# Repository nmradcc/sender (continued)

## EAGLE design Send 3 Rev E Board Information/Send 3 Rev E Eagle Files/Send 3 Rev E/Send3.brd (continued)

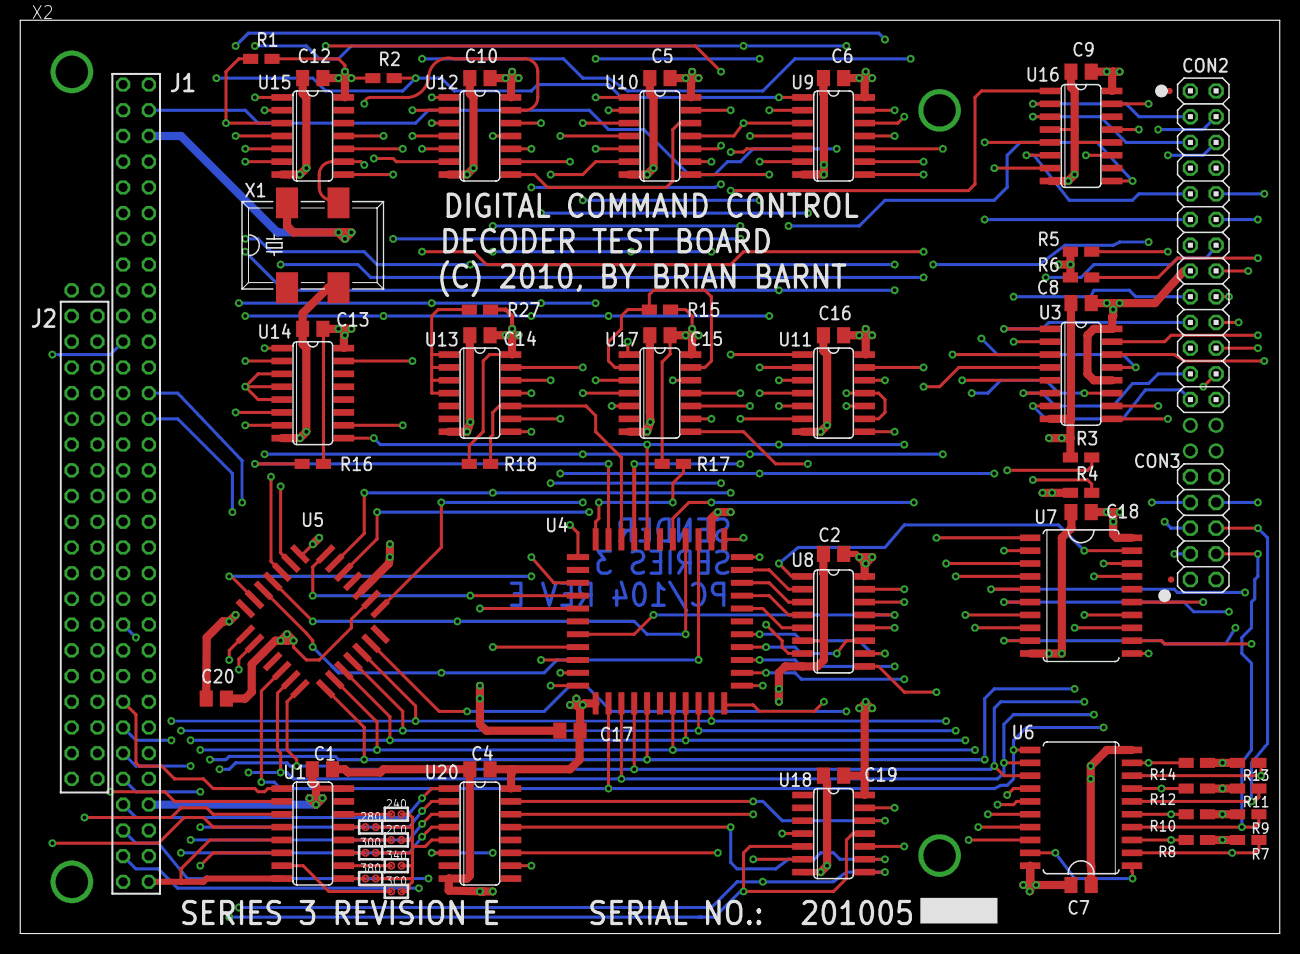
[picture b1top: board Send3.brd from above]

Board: 4 copper layers, 124.4 x 90.2 mm, 67 parts (0 on the bottom side), 118 nets.

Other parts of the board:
U$5: BORDER_AL

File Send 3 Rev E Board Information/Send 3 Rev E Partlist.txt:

Partlist

Exported from Send3.sch at 6/14/2019 9:57 PM

EAGLE Version 9.2.2 Copyright (c) 1988-2018 Autodesk, Inc.

Assembly variant: 

Part     Value          Device            Package        Library     Sheet

C1                      C-USC0805K        C0805K         Project Lib 2
C2                      C-USC0805K        C0805K         Project Lib 2
C4                      C-USC0805K        C0805K         Project Lib 3
C5                      C-USC0805K        C0805K         Project Lib 4
C6                      C-USC0805K        C0805K         Project Lib 6
C7                      C-USC0805K        C0805K         Project Lib 6
C8                      C-USC0805K        C0805K         Project Lib 6
C9                      C-USC0805K        C0805K         Project Lib 6
C10                     C-USC0805K        C0805K         Project Lib 4
C12                     C-USC0805K        C0805K         Project Lib 3
C13                     C-USC0805K        C0805K         Project Lib 4
C14                     C-USC0805K        C0805K         Project Lib 4
C15                     C-USC0805K        C0805K         Project Lib 4
C16                     C-USC0805K        C0805K         Project Lib 4
C17                     C-USC0805K        C0805K         Project Lib 5
C18                     C-USC0805K        C0805K         Project Lib 5
C19                     C-USC0805K        C0805K         Project Lib 5
C20                     C-USC0805K        C0805K         Project Lib 5
CON2                    PINHD-2X13        2X13           pinhead     6
CON3                    PINHD-2X5         2X05           pinhead     6
JMPR2                   JUMPER            SOLDER_BRIDGE  Project Lib 2
JMPR3                   JUMPER            SOLDER_BRIDGE  Project Lib 2
JMPR4                   JUMPER            SOLDER_BRIDGE  Project Lib 2
JMPR5                   JUMPER            SOLDER_BRIDGE  Project Lib 2
JMPR6                   JUMPER            SOLDER_BRIDGE  Project Lib 2
JMPR7                   JUMPER            SOLDER_BRIDGE  Project Lib 2
JMPR8                   JUMPER            SOLDER_BRIDGE  Project Lib 2
R1       10K            R-US_0805W        R0805W         Project Lib 5
R2       10K            R-US_0805W        R0805W         Project Lib 5
R3       10K            R-US_0805W        R0805W         Project Lib 6
R4       10K            R-US_0805W        R0805W         Project Lib 6
R5       10K            R-US_0805W        R0805W         Project Lib 6
R6       10K            R-US_0805W        R0805W         Project Lib 6
R7       10K            R-US_0805W        R0805W         Project Lib 6
R8       10K            R-US_0805W        R0805W         Project Lib 6
R9       10K            R-US_0805W        R0805W         Project Lib 6
R10      10K            R-US_0805W        R0805W         Project Lib 6
R11      10K            R-US_0805W        R0805W         Project Lib 6
R12      10K            R-US_0805W        R0805W         Project Lib 6
R13      10K            R-US_0805W        R0805W         Project Lib 6
R14      10K            R-US_0805W        R0805W         Project Lib 6
R15      10K            R-US_0805W        R0805W         Project Lib 4
R16      10K            R-US_0805W        R0805W         Project Lib 3
R17      10K            R-US_0805W        R0805W         Project Lib 3
R18      10K            R-US_0805W        R0805W         Project Lib 3
R27      10K            R-US_0805W        R0805W         Project Lib 5
U1       74AHC138D      74AHC138D         SO16           Project Lib 2
U3       AM26C32CD      AM26C32CD         SO16           Project Lib 6
U4                      8255A-S           PLCC44         Project Lib 3
U5       8254           8254              PLCC28S        Project Lib 4
U6       74ACT540       74540             SO20W          Project Lib 6
U7       74LS273DW      74LS273DW         SO20W          74xx-us     6
U8       74HCT166D      74HCT166D         SO16           Project Lib 5
U9       74ACT74D       7474D             SO14           Project Lib 5
U10      74ACT08D       74AC08D           SO14           Project Lib 4
U11      74ACT02D       74AC02D           SO14           Project Lib 4
U12      74ACT00D       74AC00D           SO14           Project Lib 4
U13      74ACT74D       7474D             SO14           Project Lib 5
U14      74ACT161D      74161D            SO16           Project Lib 5
U15      74AC04D        74AC04D           SO14           Project Lib 3
U16      AM26C31CD      AM26C31CD         SO16           Project Lib 6
U17      74ACT74D       7474D             SO14           Project Lib 4
U18      74ACT02D       74ACT02D          SO14           Project Lib 3
U20      74AHC138D      74AHC138D         SO16           Project Lib 2
X1                      CRYSTAL_RES-1100S 1100S          crystal     4
X2       PC104_CARD1    PC104_CARD1       PC104-STANDARD Project Lib 2

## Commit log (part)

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2020-06-02 Add the default color to the color tables
2020-06-02 Add a Major Tasks section
2020-06-02 Add options to help to all of the sub-catagories Remove the led command and make it a variable Use ResetColor when restoring the previous color
2020-06-02 Use ResetColor when restoring the previous color Use the default background color in dir
2020-06-02 Zero copy packet queue for the DCC track generator
2020-10-26 Dont wait for IsPacketComplete
2020-10-26 Dont wait
2020-10-26 Change timer to 32 bit
2020-10-26 Change to 32 bit timer
2020-10-26 Change script task stack size
2020-10-26 Add HAL_UART_ReceiveReady
2020-10-26 Put a V4 ifdef around time
2020-10-26 Lots of porting changes
2020-10-26 Fix all the build packet calls for 32 bit
2020-10-26 Change to 32 bit timers
2020-12-07 Chage the 2 & 3 to H & B
2020-12-07 Change the 2,3 to H,B Change the Direction Spped Warning if in percent mode
2020-12-07 Change the pin for AR1
2020-12-07 Add input pins
2020-12-07 Move code to main
2020-12-07 New Input module
2020-12-07 Add inputs command
2020-12-07 Add the ADC 3 code Add the Timer 4 code
2020-12-08 Remove an unused function and other code cleanup
2020-12-12 Cab display state while Send is running
2020-12-12 Cab display state while the Command Station to Track connection is disabled
2020-12-12 Change the 'packet' command so the count is one based Add the rem statment to the begginig of the packet file
2020-12-12 Add the Send and Track states
2020-12-21 Add DeleteCurrentRecall
2020-12-21 Add GetInputs
2020-12-21 Add an inputs variable
2020-12-21 Add issue to add an AND operator
2020-12-21 Add an inputs variable Add packets to help
2020-12-21 Re-write ShSendPacket
2020-12-21 Correct the pin and port numbers
2020-12-21 Bump revision
2020-12-21 Fix headers
2020-12-31 Reverse the polarity
2020-12-31 Add a loopcount variable
2020-12-31 Update issues
2020-12-31 Make Inputs a global so it can be used as a variable
2020-12-31 Add loop count Add Inputs
2020-12-31 Update project
2020-12-31 Adding Card Contents
2020-12-31 For some reason, I got a compile error on the "user_diskio.h" include, so I commented it out and put the extern in the source
2020-12-31 Add an extern for kbhit Add extern for GetLoopCount
2020-12-31 Add AND (&&) and NOT AND (!&) conditionals Fix if-else-endif Remove the Inputs command, it is now a variable
2020-12-31 Remove the Inputs command, it is now a variable Remove the YModem command Add the two ZModem commands Output the command buffer if the command is not found
2020-12-31 Add ZModem
2020-12-31 Correct bit counts and add the 'help' comment line
2021-01-04 Revised Timer1, Timer2 to HAL_GetTick functionality
2021-01-06 Added CDC & started MSC+CDC
2021-01-09 remove the argument
2021-01-09 Add issues
2021-01-09 Correct and enhance the Cab and Loco commands
2021-01-09 change the structure name (didn't match the current structure)
2021-01-12 Update document
2021-01-12 Remove
2021-01-19 Add in case we unable ExFAT
2021-01-19 Move ShellColor table Add more notes to Echo
2021-01-19 Remove LED debug lines
2021-01-20 Add the variable to led and track so they can be tested in scripts Change the dat set so that it pays attention to the date format and accepts three letter months in addition to numeric Try and fix t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
2021-01-20 Add comment and correct counts
2021-01-20 Add 5th (user button) input
2021-01-20 Add and update issues
2021-01-20 Change version number so that the three fields display
2021-01-20 Add externs to the time and date format settings
2021-01-20 Make GreenParttern a global so it can be included in the variables table
2021-01-20 Make version three fields Display the time using the time format setting Add the 5th (User button) input Allow the time to be entered in 12 hour format (regardless of the time format setting) Retrun 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
2021-01-22 Re-organize the pin defines
2021-01-22 Change the way the User Button is read to make the polarity decision easier
2021-01-22 Comment out the GPIO for ADC - it was interfering with the LED
2021-01-26 Move most of the issues to GitHub
2021-01-26 Change CR to NL and add CR
2021-01-26 Add ShCR
2021-01-26 Add ShCR Change the 'echo' CR to call sHCR and add NL to call ShNL
2021-02-01 Kkobel work (#6)
    * Initial Commit
    * Up version
    Change RCC clock source
    * Change the malloc & free calls
    * Change the date variable help
    Add date format choices
2021-05-11 Make color table dark/light for theme Replace Tasks with direct FreeRTOS calls instead of the ST layer
2021-05-11 Use the color theme
2021-05-11 Add theme variable
2021-05-11 Replace timeout constants
2021-08-25 return the ACK_STATUS from GetAck instead of an uint8
2021-08-25 Add Input 6 (the ACK ststus)
2021-08-25 Add Build Date, Track Current and Track Voltage
2021-08-25 add ACK to the inputs
2021-08-25 use PortMalloc instead of malloc
2021-08-25 make sure the ADC module is enabled
2021-08-25 correction to the track queue
2021-08-25 add the ShSendPacket command
2021-08-25 DCC track corrections
2021-08-25 add the ADC and DMA interrupt handlers
2021-08-25 update the ADC init from a seperate cube project
2021-08-25 add a shell track resource add some track resource function externs
2021-08-25 change teh stack and heap sizes
2021-08-25 reference to the new library
2021-08-25 add an implemention note
2021-08-25 modify the function event values
2021-08-25 add stdarg.h
2021-08-25 add a loop and timeout for sending packets to the track
2021-08-25 modify call for V4
2021-08-25 remove comments, but otherwise no changes
2021-11-14 Build packets for when there are no packets to send (idle, rease, ones, zeros) Select the correct packet when there are no packets to send Remove the 'scope' output for any repeating packets
2021-11-14 Add ones and zeros to track idle
2021-11-14 Add track_idle and track_lock variable strings
2021-11-14 Add VAR_TYPE_TRACK_IDLE to the init code
2021-11-14 Add track_idle and track_lock
2021-11-14 Add track_idle and track_lock variables
2021-11-14 Add a default case
2021-11-14 Change the OpenTrack to the Shell instead of the Command Station
2021-11-14 Add new line to the ShCR command
2021-11-14 Add a 'scope' option to the packet command Clear the old packet when building a new one
2021-11-14 Satically allocate the USB Buffer (remove Malloc)
2021-11-21 Don't open the track at startup
2021-11-21 Set the Cab state to 0 when it is registered
2021-11-21 Return the lengths for all packet builders
2021-11-21 Return the packet length for all packet builders
2021-11-21 More work on Service mode
2021-11-21 Better management of the Active and Inactice Cab arrays
2021-11-21 Add a Cab state to display the status of the Track resource
2021-11-21 Change the prototype of the Cab Handler
2021-11-21 Continued work on the Ack detection
2021-11-21 Bump the Version
2021-11-21 Continued work on getting the tester to function
2023-09-19 Update Card Contents
2023-09-19 Command Station Update
2023-09-19 Shell upgrades
2023-09-19 Progect Updates
2023-09-19 Net Update
2023-09-19 Middleware updates
2023-09-19 Port updates
2023-09-19 Timer update
2023-09-19 remove the enum name
2023-09-19 including stdio.h causes conflicts
2023-09-19 fix the extern to gnetif
2023-09-19 change the name of the DHCP variable
2023-09-19 update main
2024-04-01 Update Card
2024-04-01 New Card Scripts
2026-02-10 from archive V3 B.5.11.5
2026-02-10 Update README with version and build info
    Add version information and build number to README
2026-02-10 add back built bin
2026-02-10 Add link to BOX archive in README
2026-02-10 inital refactor V3 update tools
2026-02-10 Revise README for B 5.11.5 branch changes
    Updated README to reflect branch refactor and build tool requirements.
2026-02-10 Update README to discourage legacy .INI file usage
    Clarified the usage of legacy .INI files in the README.
2026-02-10 Update README to discourage .INI file usage
    Clarify documentation regarding legacy .INI file usage.
2026-02-10 Update README to reflect changes in Visual Source Safe
2026-03-08 remove bat files add debug launch parameters
2026-03-11 robust name/extension improved parser
2026-03-12 more launch options
2026-03-12 correct spelling
2026-03-14 init co-mcu
2026-03-14 initial split projects
2026-03-14 launch
2026-03-14 move HW
2026-03-14 563 clean up
2026-03-14 usb tweaks
2026-03-14 still not detecting USB
2026-03-16 usb enumerating
2026-03-16 smoke test working communicating
2026-03-16 timer 5 PA0
2026-03-16 revise build
2026-03-30 send selftest
2026-04-01 add extra com port parameters
2026-04-01 interface
2026-04-01 reorder self/smoke tests
2026-04-07 reset stats
2026-04-09 chunked send packets
2026-04-09 no legacy vector tests
2026-04-09 remove legacy port and critical
2026-04-09 simplified
2026-04-09 remove 8255/54
2026-04-11 reorder folders remove old doc
2026-04-11 warning
2026-04-11 dup logpkt from legacy
2026-04-11 more debug logging match
2026-04-27 fix io in polarity
2026-04-28 log match
2026-04-29 workspace
2026-04-30 V4 initial refactor cleanup
2026-04-30 ignore .clangd
2026-05-08 bypass hw backend when logpkt set
2026-05-08 bypass hw backend when logpkt set (#25)
2026-05-09 add bin gen also
2026-05-09 add .bin generator (#26)
    * bypass hw backend when logpkt set
    * add bin gen also
2026-06-13 add yellow hartbeat led
2026-06-15 version dump improvements
2026-06-15 heartbeat led and mcu version dump improvements (#27)
    * bypass hw backend when logpkt set
    * add bin gen also
    * add yellow hartbeat led
    * version dump improvements
